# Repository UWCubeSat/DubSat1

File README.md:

# DubSat1 Repository

This is the University of Washington CubeSat Team's DubSat1
library.

More info about our club can be visited [here](http://earthweb.ess.washington.edu/space-propulsion/cubesat.php)

## Repository Contents
DubSat1 is a repository containing configuration-managed assets for the University of Washington's Dubsat-1 (DS-1) satellite, scheduled to fly at the end of the summer 2018.  Assets included here include source code for all subsystems, PCB and schematic design files, and physical design and analysis assets.  

## Repository Branches
The following branches are maintained in the DubSat1 project.  Please follow the guidelines provided.
* master:  Should ALWAYS be kept fully-functional, and ideally tagged to reflect completed milestones/sprint payloads, etc.  *NO CHECKINS SHOULD BE MADE DIRECTLY INTO THIS BRANCH* except by integration managers.
* develop:  Most work should be either committed to this branch, or a feature/* branch based off of develop (see below).  Non-coding work (e.g. PCB board design or SolidWORKS iterations) can go into this branch directly.
* feature/<featurename>:  Most significant chunks of coding work should be done in small, separate feature branches.  Feel free to create these as needed, but do name them using the indicated scheme e.g. "feature/I2Cv2".  However, *BE SURE TO BASE NEW FEATURE BRANCHES OFF OF DEVELOP* and not the master branch.  This helps quite a bit in certain merge scenarios down the road.

## Repository Directories
### /src
Contains the source code designed to run on prototype, test, or flight hardware.  Sub-directories include:

* /src/dsbase:	Here are the core satellite base libraries, used to wrap access to common functionality across the spacecraft, including SPI, I2C and CAN bus access, debug functionality, and general board support packages.
* /src/ssmods:	Standing for "sub-system modules", it is a hard requirement that each subdirectory under ssmods corresponds to one executable unit, to be deployed on one compute element (generally either the MSP430 or MSP432) on the spacecraft, and only the machine-independent files should be saved here (though the .gitignore file SHOULD be setup to screen out most commonly occurring machine-specific build artifacts that we don't want to store).  Anything that doesn't fit this description should go elsewhere.
* /src/devmods:	Used to store experimental work for prototypes or test hardware that is "close" to being moved over to a "real" subsystem module, sort of as a staging ground.  Projects under this folder should also be MSP43x-based, as well.
* /src/dsbase-dev:  GOING AWAY VERY SOON, JeffC will coordinate with folks that typically write to this folder to make the transition to the new branch-based model sometime later in sprint 3.

### /ref
Reference material that is dynamic, including current pin assignments, microcontroller peripheral instance usage, libray usage notes, and Code Composer Studio setup requirements.  Static content - e.g. product datasheets - should be stashed on the team wiki instead.

### /teams
This set of folders is for individual teams to store whatever other assets they have that a) need any level of change tracking, or b) general coordination between multiple contributors, and c) aren't massive.  As a point of reference, each Git repo needs to stay under about 1GB, so if you are routinely checking in 25MB file chunks, please contact the CDH team for alternative arrangements - it can really add up.

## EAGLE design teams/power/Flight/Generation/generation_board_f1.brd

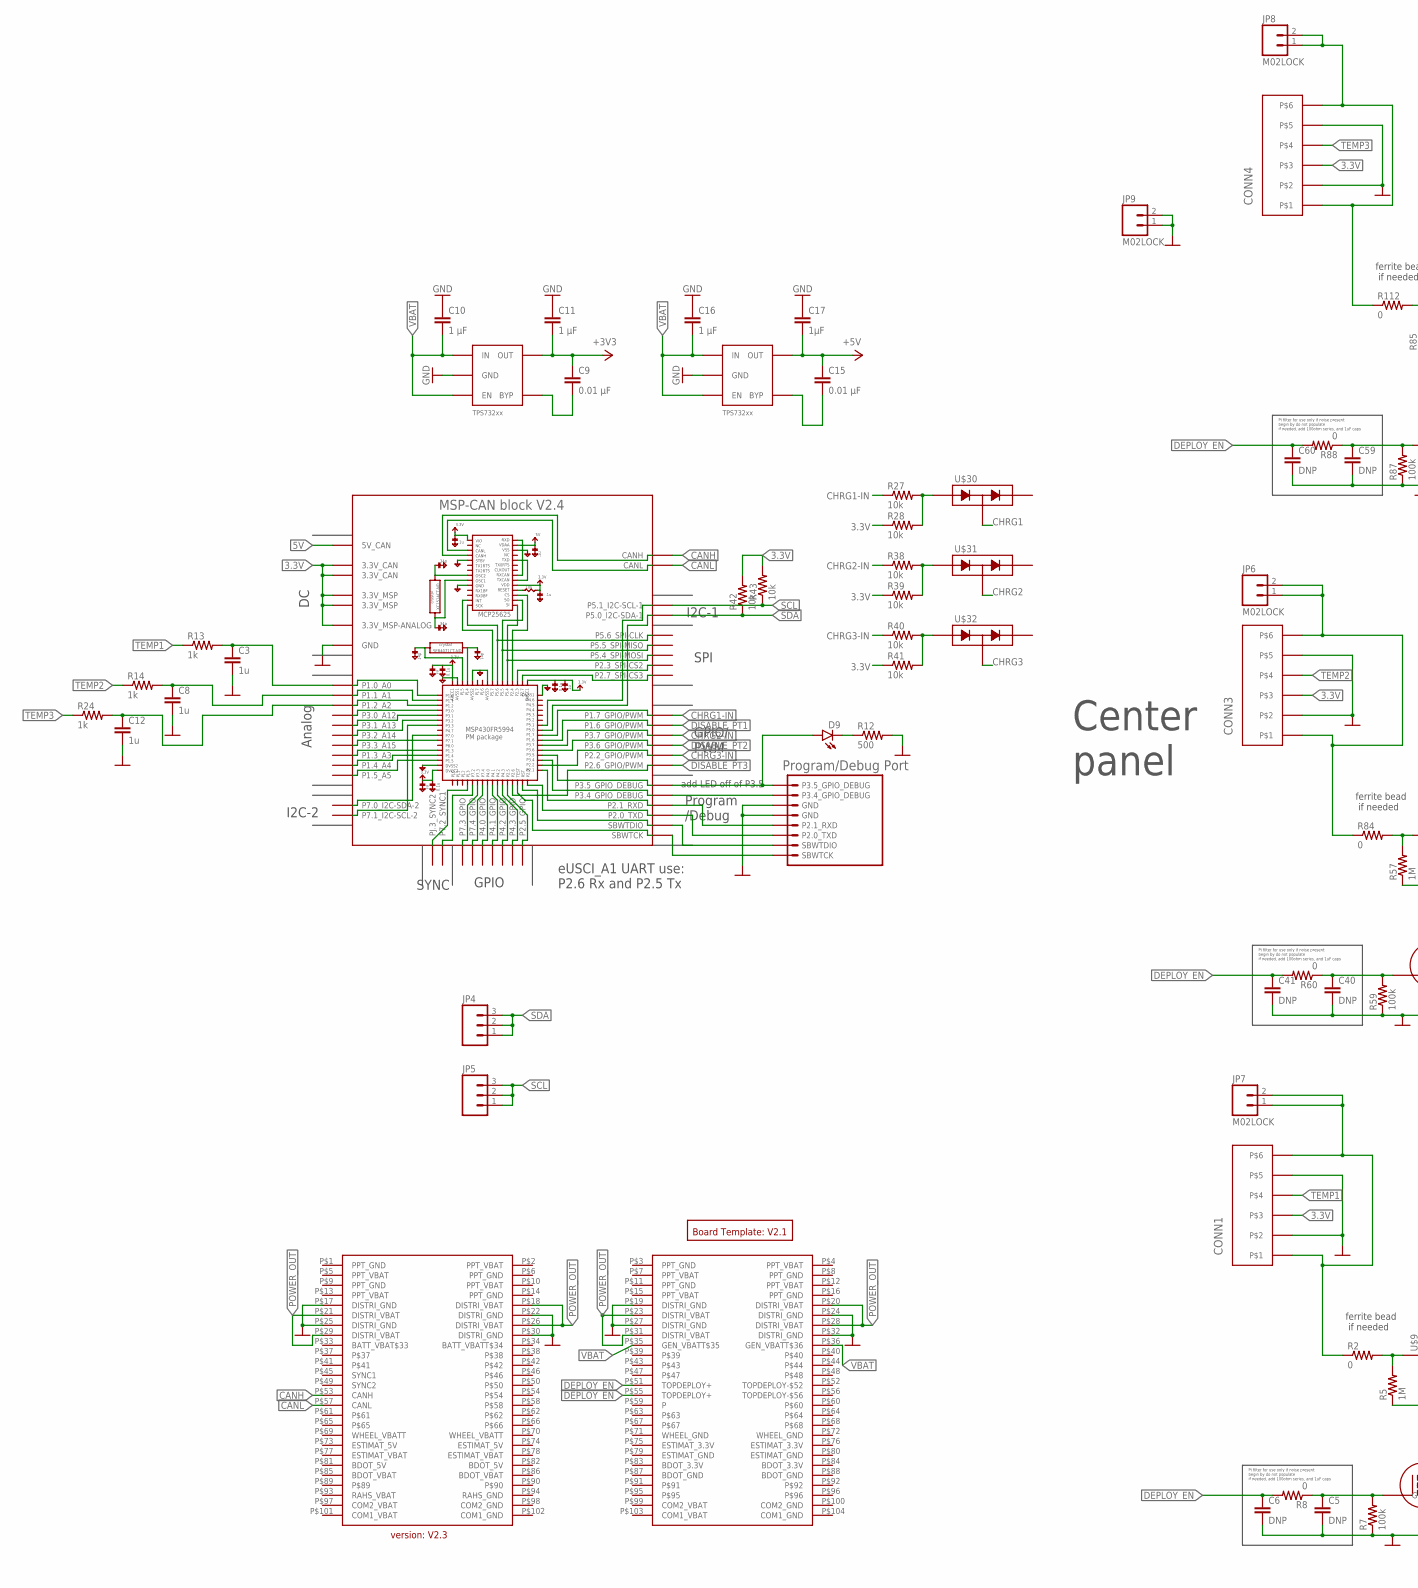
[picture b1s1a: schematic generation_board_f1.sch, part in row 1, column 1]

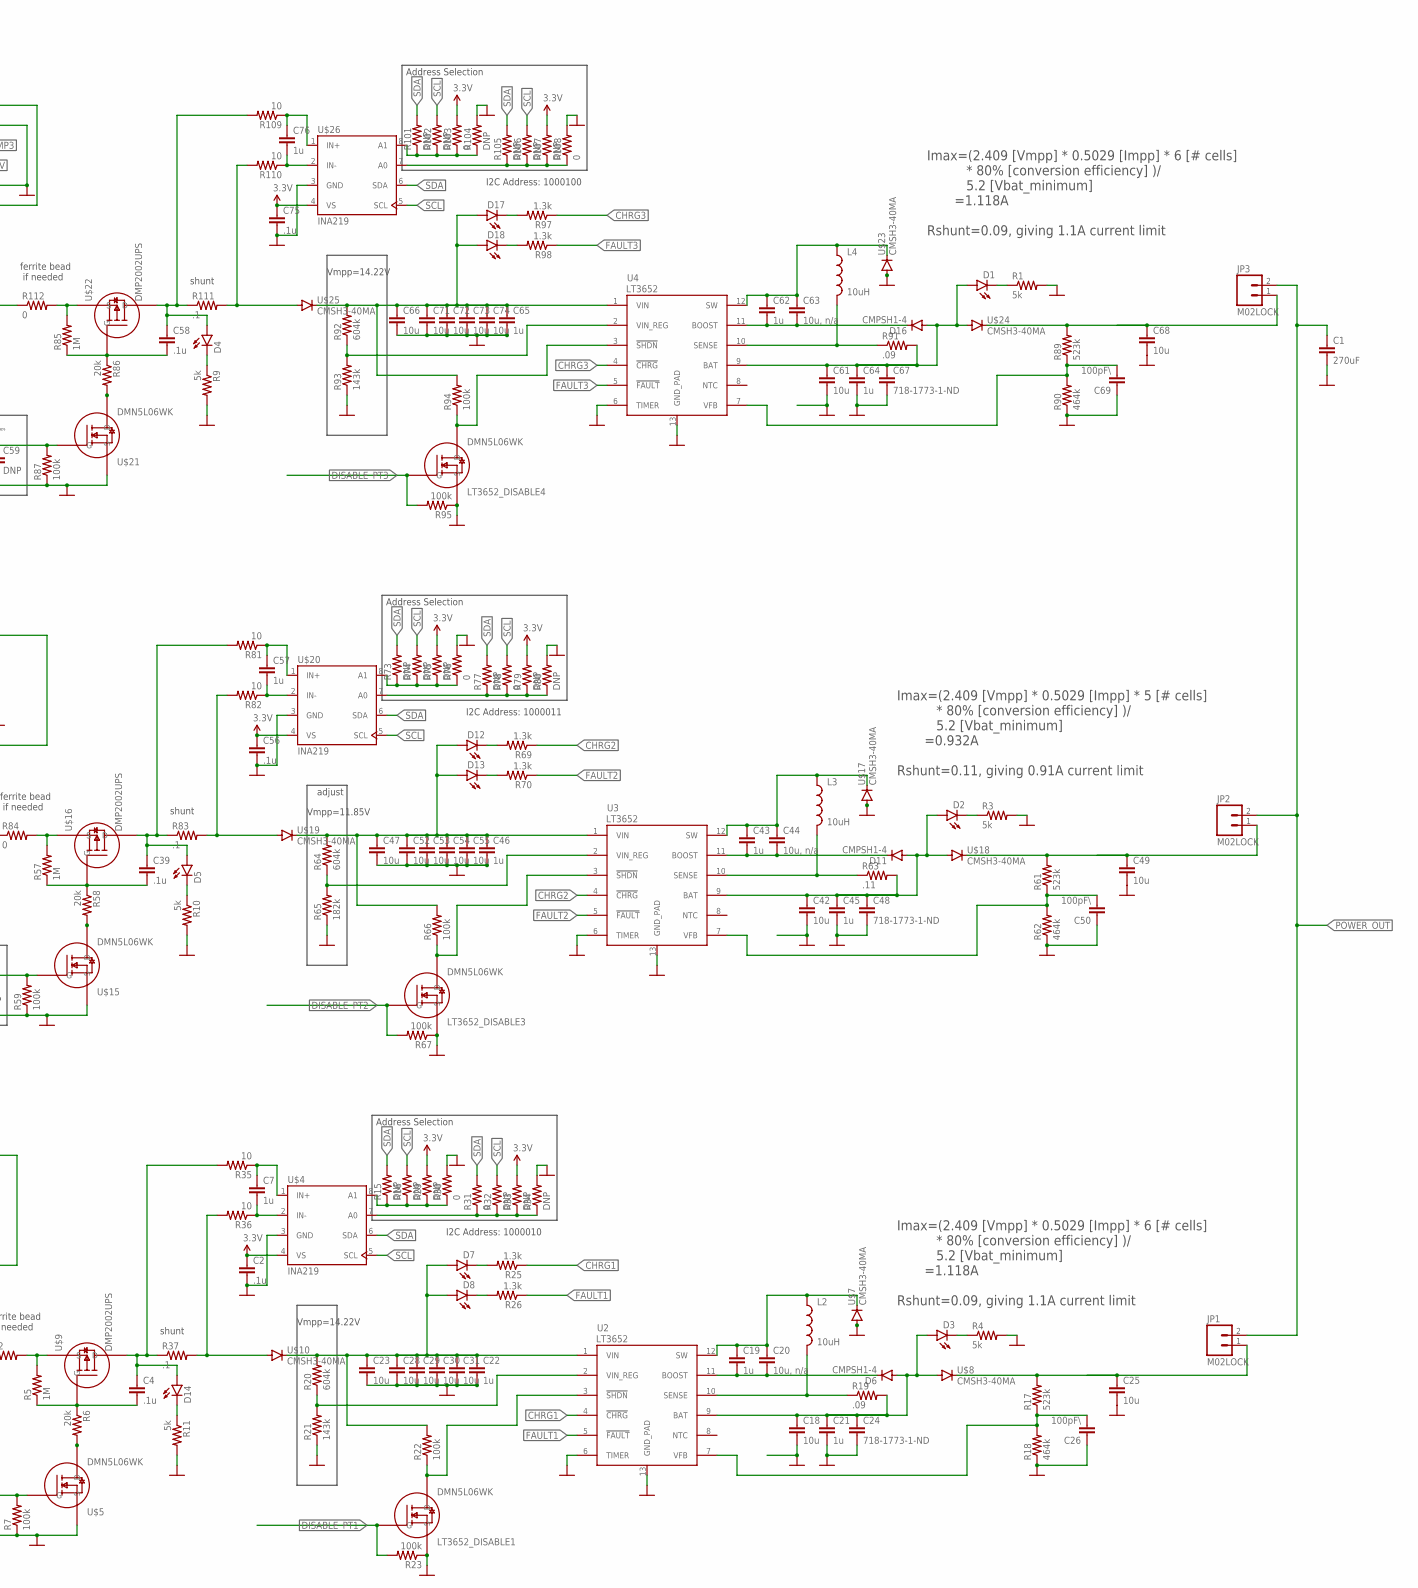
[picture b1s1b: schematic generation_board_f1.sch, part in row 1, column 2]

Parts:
BLK1: MSP-CAN_BLOCK
C1: 270uF; 2917
C2, C4, C39, C56, C58, C75: .1u; 0805
C3, C7, C8, C12, C19, C21, C22, C43, C45, C46, C57, C62, C64, C65, C76: 1u; 0805
C5, C6, C40, C41, C59, C60: DNP; 0805
C9, C15: 0.01 μF; 0805
C10, C11, C16: 1 μF; 0805
C17: 1μF; 0805
C18, C25, C42, C49, C61, C68: 10u; 0805
C20, C44, C63: 10u, n/a; 0805
C23, C28, C29, C30, C31, C47, C52, C53, C54, C55, C66, C71, C72, C73, C74: 10u; 1210
C24, C48, C67: 718-1773-1-ND; 2917
C26, C50, C69: 100pF\; 0805
CONN1, CONN3, CONN4: PICOLOCK_6
D1, D2, D3, D4, D5, D7, D8, D9, D12, D13, D14, D17, D18: LED; LED-1206
D6, D11, D16: CMPSH1-4; SOT23-3
JP1, JP2, JP3, JP6, JP7, JP8, JP9: M02LOCK; 1X02_LOCK
JP4, JP5: M03LOCK; 1X03_LOCK
L2, L3, L4: 10uH; VISHAY_SERIES_01
LT3652_DISABLE1, LT3652_DISABLE3, LT3652_DISABLE4: DMN5L06WK; SOT-323
R1, R3, R4, R9, R10, R11: 5k; 0805
R2, R8, R30, R31, R60, R76, R78, R84, R88, R103, R108, R112: 0; 0805
R5, R57, R85: 1M; 0805
R6, R58, R86: 20k; 0805
R7, R22, R23, R59, R66, R67, R87, R94, R95: 100k; 0805
R12: 500; 0805
R13, R14, R24: 1k; 0805
R15, R16, R29, R32, R33, R34, R73, R74, R75, R77, R79, R80, R101, R102, R104, R105, R106, R107: DNP; 0805
R17, R61, R89: 523k; 0805
R18, R62, R90: 464k; 0805
R19, R91: .09; R2010
R20, R64, R92: 604k; 0805
R21, R93: 143k; 0805
R25, R26, R69, R70, R97, R98: 1.3k; 0805
R27, R28, R38, R39, R40, R41, R42, R43: 10k; 0805
R35, R36, R81, R82, R109, R110: 10; 0805
R37, R83, R111: .1; R2010
R63: .11; R2010
R65: 182k; 0805
U2, U3, U4: LT3652; MSOP-12_GND
U5, U7: TPS732XX; SOT-23-5
U$1: PC104_CONNECTOR
U$2: BOARD_TEMPLATE1; BOARD_TEMPLATE
U$3: PROGRAM/DEBUG_PORT; 1X08_CONNECTOR
U$4, U$20, U$26: INA219; SOT-23-8
U$5, U$15, U$21: DMN5L06WK; SOT-323
U$7, U$8, U$10, U$17, U$18, U$19, U$23, U$24, U$25: CMSH3-40MA; SMA-DIODE
U$9, U$16, U$22: DMP2002UPS; POWERDI5060-8
U$30, U$31, U$32: ONSEMI_DIODE_BAT54SL; SOT23-3

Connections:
3.3V: BLK1.3.3V@CAN1 (3.3V_CAN), BLK1.3.3V@CAN2 (3.3V_CAN), BLK1.3.3V@MSP1 (3.3V_MSP), BLK1.3.3V@MSP2 (3.3V_MSP), BLK1.3.3V_ANALOG@MSP2 (3.3V_MSP-ANALOG), C2.1, C9.1, C11.2, C56.1, C75.1, CONN1.P$3, CONN3.P$3, CONN4.P$3, R28.1, R29.2, R33.2, R39.1, R41.1, R42.2, R43.2, R75.2, R79.2, R103.2, R107.2, U5.P$5 (OUT), U$4.4 (VS), U$20.4 (VS), U$26.4 (VS)
5V: BLK1.5V (5V_CAN), C15.1, C17.2, U7.P$5 (OUT)
BAT1: C18.1, C21.1, C24.1, D3.A, D6.1 (A), R19.2, U2.9 (BAT), U$8.A
BAT2: C42.1, C45.1, C48.1, D2.A, D11.1 (A), R63.2, U3.9 (BAT), U$18.A
BAT3: C61.1, C64.1, C67.1, D1.A, D16.1 (A), R91.2, U4.9 (BAT), U$24.A
BOOST1: C19.2, C20.2, D6.3 (C), U2.11 (BOOST)
BOOST2: C43.2, C44.2, D11.3 (C), U3.11 (BOOST)
BOOST3: C62.2, C63.2, D16.3 (C), U4.11 (BOOST)
CANH: BLK1.CANH, U$1.P$53 (CANH)
CANL: BLK1.CANL, U$1.P$57 (CANL)
CHRG1: R25.1, U2.4 (!CHRG), U$30.3
CHRG1-IN: BLK1.P1.7_GPIO/PWM, R27.1
CHRG2: R69.1, U3.4 (!CHRG), U$31.3
CHRG2-IN: BLK1.P3.7_GPIO/PWM, R38.1
CHRG3: R97.1, U4.4 (!CHRG), U$32.3
CHRG3-IN: BLK1.P2.2_GPIO/PWM, R40.1
DEPLOY_EN: C6.1, C41.1, C60.1, R8.2, R60.2, R88.2, U$1.P$51 (TOPDEPLOY+), U$1.P$55 (TOPDEPLOY+)
DISABLE_PT1: BLK1.P1.6_GPIO/PWM, LT3652_DISABLE1.1 (G), R23.2
DISABLE_PT2: BLK1.P3.6_GPIO/PWM, LT3652_DISABLE3.1 (G), R67.2
DISABLE_PT3: BLK1.P2.6_GPIO/PWM, LT3652_DISABLE4.1 (G), R95.2
FAULT1: R26.1, U2.5 (!FAULT)
FAULT2: R70.1, U3.5 (!FAULT)
FAULT3: R98.1, U4.5 (!FAULT)
GND: BLK1.GND@1 (GND), BLK1.GND@2 (GND), BLK1.GND@3 (GND), BLK1.GND@4 (GND), BLK1.GND@5 (GND), BLK1.GND@7 (GND), BLK1.GND@8 (GND), BLK1.GND@9 (GND), BLK1.GND@10 (GND), BLK1.GND@11 (GND), BLK1.GND@12 (GND), BLK1.GND@13 (GND), BLK1.GND@14 (GND), BLK1.GND@15 (GND), BLK1.GND@16 (GND), BLK1.GND@17 (GND), BLK1.GND@26 (GND), C1.2, C2.2, C3.2, C5.2, C6.2, C8.2, C10.1, C11.1, C12.2, C16.1, C17.1, C18.2, C21.2, C22.2, C23.2, C24.2, C25.2, C26.1, C28.2, C29.2, C30.2, C31.2, C40.2, C41.2, C42.2, C45.2, C46.2, C47.2, C48.2, C49.2, C50.1, C52.2, C53.2, C54.2, C55.2, C56.2, C59.2, C60.2, C61.2, C64.2, C65.2, C66.2, C67.2, C68.2, C69.1, C71.2, C72.2, C73.2, C74.2, C75.2, CONN1.P$2, CONN1.P$5, CONN3.P$2, CONN3.P$5, CONN4.P$2, CONN4.P$5, JP9.1, JP9.2, LT3652_DISABLE1.2 (S), LT3652_DISABLE3.2 (S), LT3652_DISABLE4.2 (S), R1.2, R3.2, R4.2, R7.1, R9.2, R10.2, R11.2, R12.2, R18.1, R21.1, R23.1, R30.2, R34.2, R59.1, R62.1, R65.1, R67.1, R76.2, R80.2, R87.1, R90.1, R93.1, R95.1, R104.2, R108.2, U2.6 (TIMER), U2.13 (GND_PAD), U3.6 (TIMER), U3.13 (GND_PAD), U4.6 (TIMER), U4.13 (GND_PAD), U5.P$2 (GND), U7.P$2 (GND), U$1.P$17 (DISTRI_GND), U$1.P$19 (DISTRI_GND), U$1.P$22 (DISTRI_GND), U$1.P$24 (DISTRI_GND), U$1.P$25 (DISTRI_GND), U$1.P$27 (DISTRI_GND), U$1.P$30 (DISTRI_GND), U$1.P$32 (DISTRI_GND), U$3.5 (GND), U$3.6 (GND), U$4.3 (GND), U$5.2 (S), U$7.A, U$15.2 (S), U$17.A, U$20.3 (GND), U$21.2 (S), U$23.A, U$26.3 (GND)
IN1: R2.2, R5.2, U$9.S1 (S), U$9.S2 (S), U$9.S3 (S)
IN2: R57.2, R84.2, U$16.S1 (S), U$16.S2 (S), U$16.S3 (S)
IN3: R85.2, R112.2, U$22.S1 (S), U$22.S2 (S), U$22.S3 (S)
INA219_A0_1: R31.1, R32.1, R33.1, R34.1, U$4.7 (A0)
INA219_A0_2: R77.1, R78.1, R79.1, R80.1, U$20.7 (A0)
INA219_A0_3: R105.1, R106.1, R107.1, R108.1, U$26.7 (A0)
INA219_A1_1: R15.1, R16.1, R29.1, R30.1, U$4.8 (A1)
INA219_A1_2: R73.1, R74.1, R75.1, R76.1, U$20.8 (A1)
INA219_A1_3: R101.1, R102.1, R103.1, R104.1, U$26.8 (A1)
INA219_IN+_1: C7.1, R35.1, U$4.1 (IN+)
INA219_IN+_2: C57.1, R81.1, U$20.1 (IN+)
INA219_IN+_3: C76.1, R109.1, U$26.1 (IN+)
INA219_IN-_1: C7.2, R36.1, U$4.2 (IN-)
INA219_IN-_2: C57.2, R82.1, U$20.2 (IN-)
INA219_IN-_3: C76.2, R110.1, U$26.2 (IN-)
INPUT_PANEL1: CONN1.P$1, CONN1.P$6, JP7.1, JP7.2, R2.1
INPUT_PANEL2: CONN3.P$1, CONN3.P$6, JP6.1, JP6.2, R84.1
INPUT_PANEL3: CONN4.P$1, CONN4.P$6, JP8.1, JP8.2, R112.1
LDO_3V3_BYP2: C9.2, U5.P$4 (BYP)
LDO_5V_BYP2: C15.2, U7.P$4 (BYP)
LOAD1: R36.2, R37.2, U$10.A
LOAD2: R82.2, R83.2, U$19.A
LOAD3: R110.2, R111.2, U$25.A
unnamed: C4.2, R5.1, R6.1, U$9.G
unnamed: C5.1, R7.2, R8.1, U$5.1 (G)
unnamed: BLK1.P3.5_GPIO_DEBUG, D9.A, U$3.8 (P3.5_GPIO_DEBUG)
unnamed: BLK1.P3.4_GPIO_DEBUG, U$3.7 (P3.4_GPIO_DEBUG)
unnamed: BLK1.P2.1_RXD, U$3.4 (P2.1_RXD)
unnamed: R6.2, U$5.3 (D)
unnamed: BLK1.P2.0_TXD, U$3.3 (P2.0_TXD)
unnamed: BLK1.SBWTDIO, U$3.2 (SBWTDIO)
unnamed: BLK1.SBWTCK, U$3.SBWTCK
unnamed: D1.C, R1.1
unnamed: D2.C, R3.1
unnamed: D3.C, R4.1
unnamed: D4.C, R9.1
unnamed: C39.2, R57.1, R58.1, U$16.G
unnamed: C40.1, R59.2, R60.1, U$15.1 (G)
unnamed: LT3652_DISABLE1.3 (D), R22.1, U2.3 (!SHDN)
unnamed: D8.C, R26.2
unnamed: D7.C, R25.2
unnamed: R58.2, U$15.3 (D)
unnamed: BLK1.P1.1_A1, C8.1, R14.2
unnamed: D9.C, R12.1
unnamed: LT3652_DISABLE3.3 (D), R66.1, U3.3 (!SHDN)
unnamed: D13.C, R70.2
unnamed: D12.C, R69.2
unnamed: D14.C, R11.1
unnamed: D5.C, R10.1
unnamed: C58.2, R85.1, R86.1, U$22.G
unnamed: C59.1, R87.2, R88.1, U$21.1 (G)
unnamed: R86.2, U$21.3 (D)
unnamed: LT3652_DISABLE4.3 (D), R94.1, U4.3 (!SHDN)
unnamed: D18.C, R98.2
unnamed: D17.C, R97.2
unnamed: BLK1.P1.2_A2, C12.1, R24.2
unnamed: BLK1.P1.0_A0, C3.1, R13.2
unnamed: R27.2, R28.2, U$30.1
unnamed: R38.2, R39.2, U$31.1
unnamed: R40.2, R41.2, U$32.1
OUT1: C4.1, D14.A, R35.2, R37.1, U$9.D1 (D), U$9.D2 (D), U$9.D3 (D), U$9.D4 (D), U$9.D5 (D)
OUT2: C39.1, D5.A, R81.2, R83.1, U$16.D1 (D), U$16.D2 (D), U$16.D3 (D), U$16.D4 (D), U$16.D5 (D)
OUT3: C58.1, D4.A, R109.2, R111.1, U$22.D1 (D), U$22.D2 (D), U$22.D3 (D), U$22.D4 (D), U$22.D5 (D)
OUTPUT1: C25.1, JP1.1, R17.2, U$8.C
OUTPUT2: C49.1, JP2.1, R61.2, U$18.C
OUTPUT3: C68.1, JP3.1, R89.2, U$24.C
POWER_OUT: C1.1, JP1.2, JP2.2, JP3.2, U$1.P$18 (DISTRI_VBAT), U$1.P$20 (DISTRI_VBAT), U$1.P$21 (DISTRI_VBAT), U$1.P$23 (DISTRI_VBAT), U$1.P$26 (DISTRI_VBAT), U$1.P$28 (DISTRI_VBAT), U$1.P$29 (DISTRI_VBAT), U$1.P$31 (DISTRI_VBAT)
SCL: BLK1.P5.1_I2C-SCL-1, JP5.1, JP5.2, JP5.3, R16.2, R32.2, R43.1, R74.2, R78.2, R102.2, R106.2, U$4.5 (SCL), U$20.5 (SCL), U$26.5 (SCL)
SDA: BLK1.P5.0_I2C-SDA-1, JP4.1, JP4.2, JP4.3, R15.2, R31.2, R42.1, R73.2, R77.2, R101.2, R105.2, U$4.6 (SDA), U$20.6 (SDA), U$26.6 (SDA)
SENSE1: L2.P$2 (2), R19.1, U2.10 (SENSE)
SENSE2: L3.P$2 (2), R63.1, U3.10 (SENSE)
SENSE3: L4.P$2 (2), R91.1, U4.10 (SENSE)
SW1: C19.1, C20.1, L2.P$1 (1), U2.12 (SW), U$7.C
SW2: C43.1, C44.1, L3.P$1 (1), U3.12 (SW), U$17.C
SW3: C62.1, C63.1, L4.P$1 (1), U4.12 (SW), U$23.C
TEMP1: CONN1.P$4, R13.1
TEMP2: CONN3.P$4, R14.1
TEMP3: CONN4.P$4, R24.1
VBAT: C10.2, C16.2, U5.P$1 (IN), U5.P$3 (EN), U7.P$1 (IN), U7.P$3 (EN), U$1.P$35 (GEN_VBATT$35), U$1.P$36 (GEN_VBATT$36)
VFB1: C26.2, R17.1, R18.2, U2.7 (VFB)
VFB2: C50.2, R61.1, R62.2, U3.7 (VFB)
VFB3: C69.2, R89.1, R90.2, U4.7 (VFB)
VIN1: C22.1, C23.1, C28.1, C29.1, C30.1, C31.1, D7.A, D8.A, R20.2, R22.2, U2.1 (VIN), U$10.C
VIN2: C46.1, C47.1, C52.1, C53.1, C54.1, C55.1, D12.A, D13.A, R64.2, R66.2, U3.1 (VIN), U$19.C
VIN3: C65.1, C66.1, C71.1, C72.1, C73.1, C74.1, D17.A, D18.A, R92.2, R94.2, U4.1 (VIN), U$25.C
VIN_REG1: R20.1, R21.2, U2.2 (VIN_REG)
VIN_REG2: R64.1, R65.2, U3.2 (VIN_REG)
VIN_REG3: R92.1, R93.2, U4.2 (VIN_REG)

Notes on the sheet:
Pi filter for use only if noise present begin by do not populate if needed, add 100ohm series, and 1uF caps
Address Selection
ferrite bead if needed
shunt
adjust
Vmpp=14.22V
Center panel
Imax=(2.409 [Vmpp] * 0.5029 [Impp] * 6 [# cells] * 80% [conversion efficiency] )/ 5.2 [Vbat_minimum] =1.118A Rshunt=0.09, giving 1.1A current limit
Imax=(2.409 [Vmpp] * 0.5029 [Impp] * 5 [# cells] * 80% [conversion efficiency] )/ 5.2 [Vbat_minimum] =0.932A Rshunt=0.11, giving 0.91A current limit
Vmpp=11.85V
I2C Address: 1000010
I2C Address: 1000011
I2C Address: 1000100

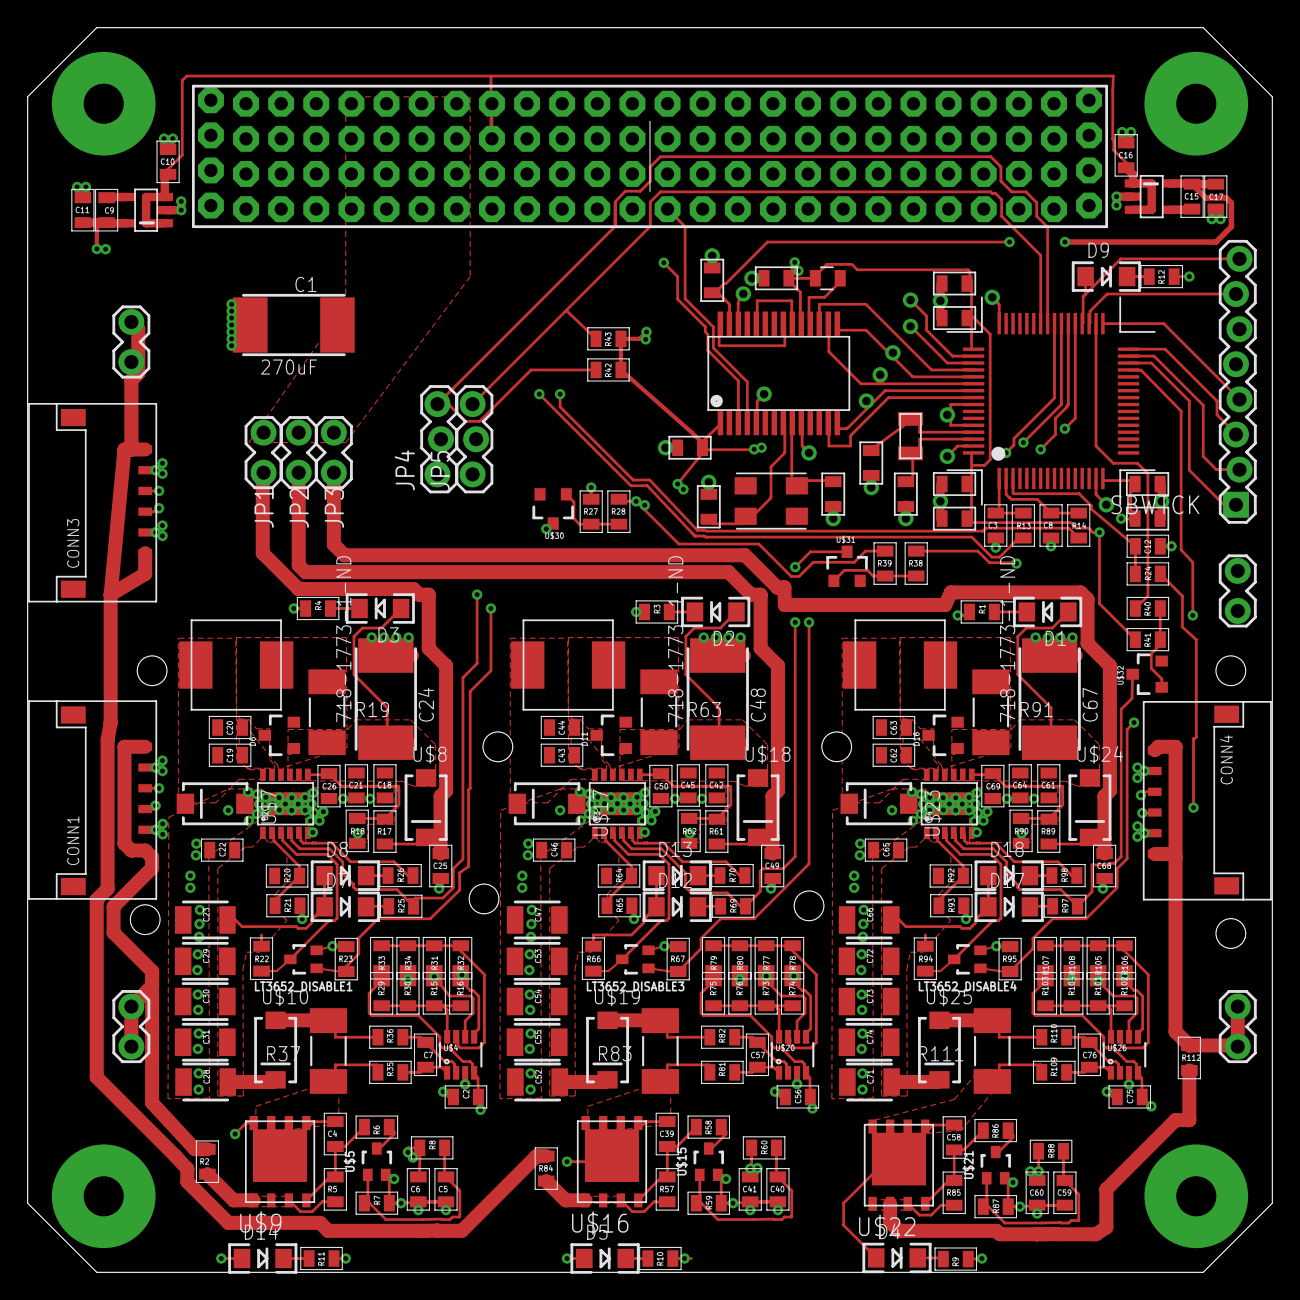
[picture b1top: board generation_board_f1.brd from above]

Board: 4 copper layers, 90.0 x 90.0 mm, 229 parts (0 on the bottom side), 112 nets.

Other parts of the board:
U$6, U$11, U$12, U$13, U$14, U$27, U$28, U$29: #2-56_BOLT_HOLE

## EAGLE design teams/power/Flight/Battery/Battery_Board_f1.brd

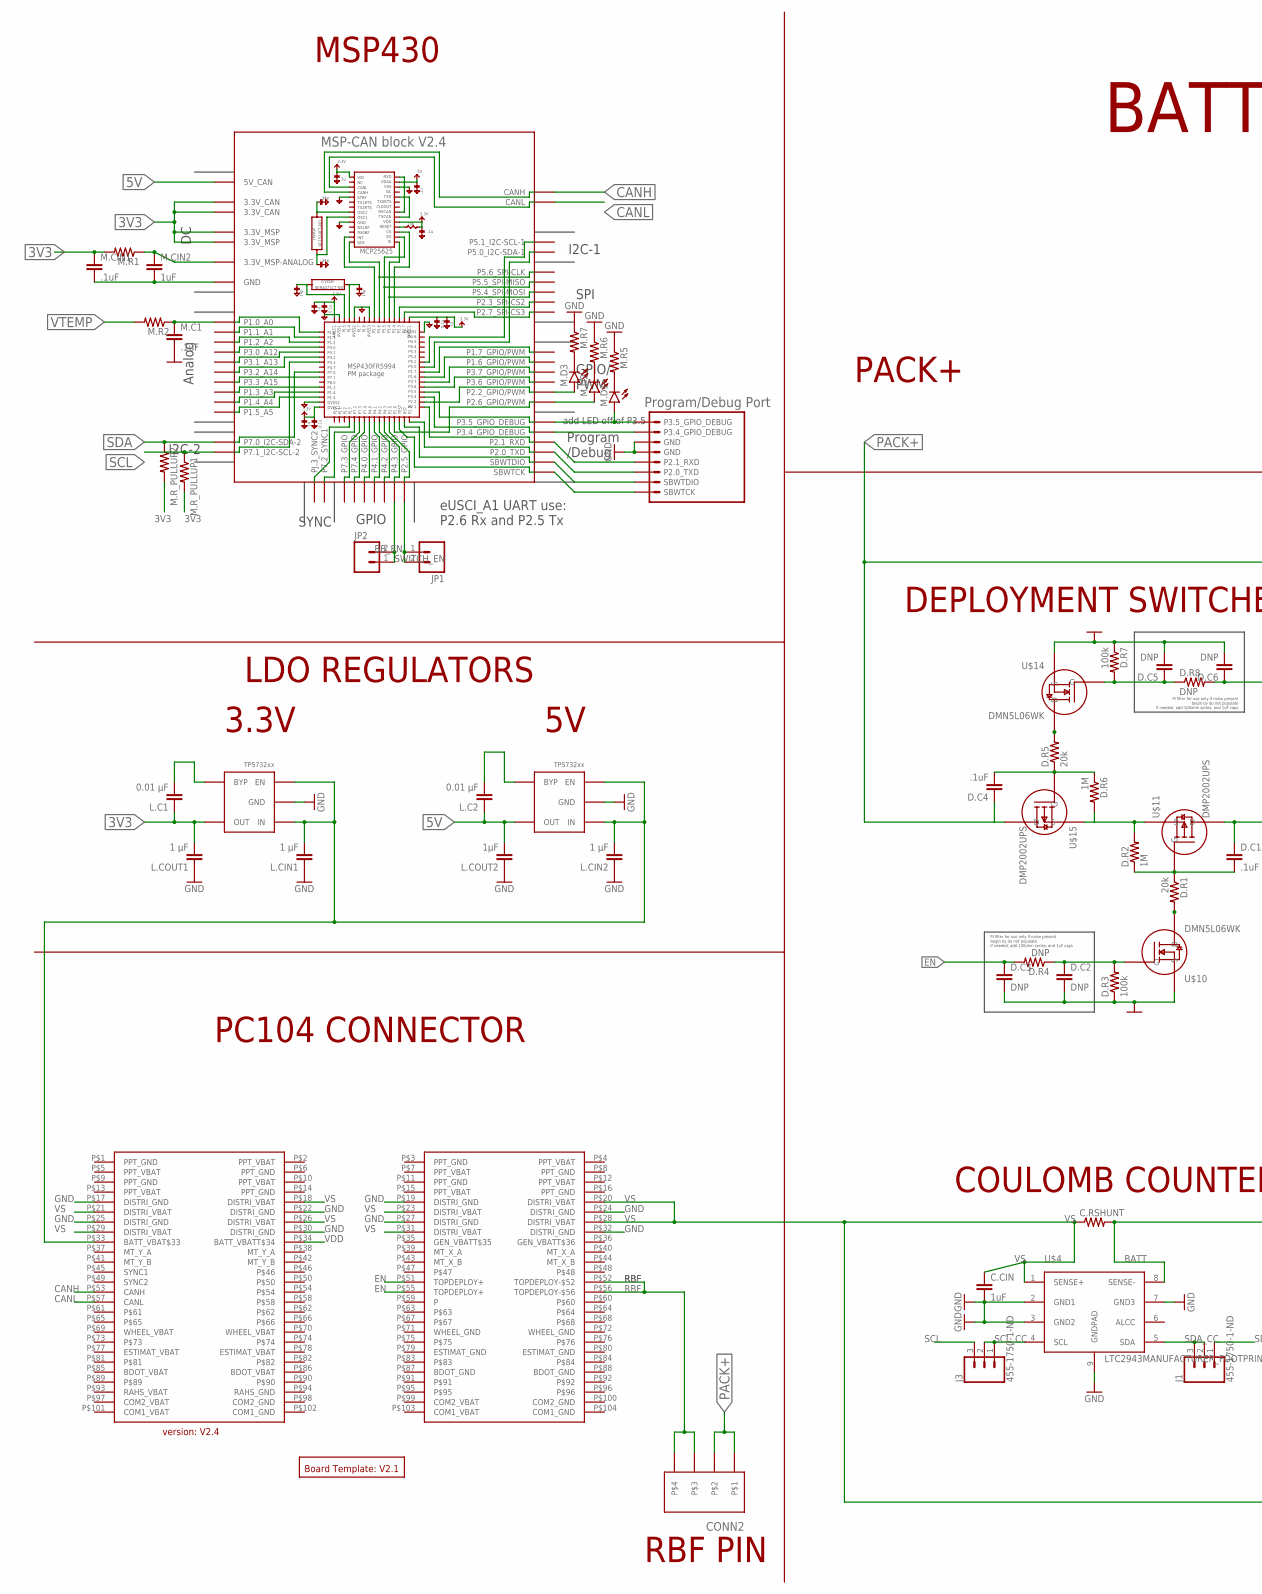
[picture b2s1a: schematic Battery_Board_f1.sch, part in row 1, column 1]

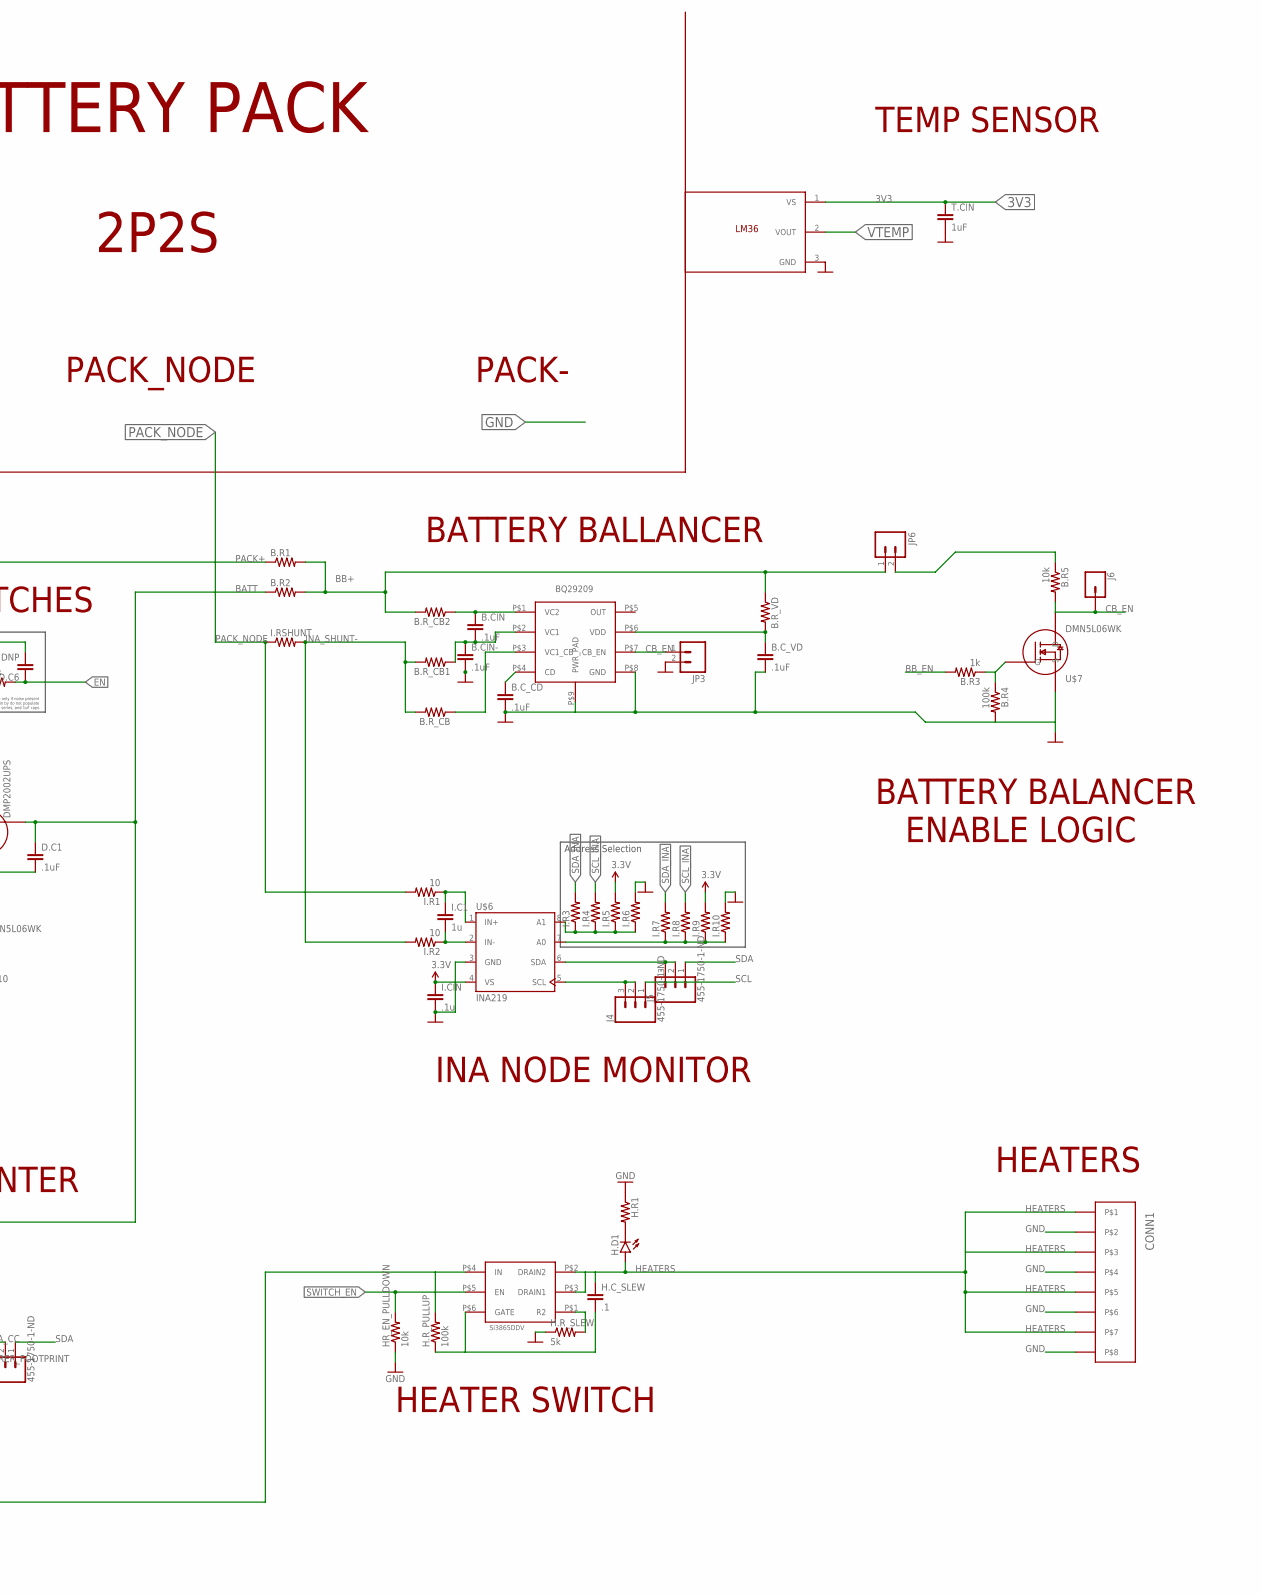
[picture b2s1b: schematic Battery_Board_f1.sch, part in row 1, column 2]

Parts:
B.CIN, B.CIN-, B.C_CD, B.C_VD: .1uF; 0805
B.R1, B.R2, B.R_CB, B.R_CB1, B.R_CB2, B.R_VD: RESISTOR0805; 0805
B.R3: 1k; 0805
B.R4: 100k; 0805
B.R5: 10k; 0805
BLK1: MSP-CAN_BLOCK
C.CIN: 1uF; 0805
C.RSHUNT: RESISTOR2512; R2512
CONN1: PICOLOCK_8PICOLOCK_8; PICOLOCK_8
CONN2: PICOLOCK_4PICOLOCK_4; PICOLOCK_4
D.C1, D.C4: .1uF; 0805
D.C2, D.C3, D.C5, D.C6, D.R4, D.R8: DNP; 0805
D.R1, D.R5: 20k; 0805
D.R2, D.R6: 1M; 0805
D.R3, D.R7: 100k; 0805
H.C_SLEW: .1; 0805
H.D1: LED; LED-1206
H.R1: RESISTOR0805; 0805
H.R_PULLUP: 100k; 0805
H.R_SLEW: 5k; 0805
HR_EN_PULLDOWN: 10k; 0805
I.C1: 1u; 0805
I.CIN: .1u; 0805
I.R1, I.R2: 10; 0805
I.R3, I.R4, I.R5, I.R6, I.R7, I.R8, I.R9, I.R10: RESISTOR0805; 0805
I.RSHUNT: RESISTOR2010; R2010
J1, J3, J4, J5: 455-1750-1-ND; 1X03
J6: CONN_01; 1X01
JP1, JP2, JP3, JP6: M02LOCK; 1X02_LOCK
L.C1, L.C2: 0.01 μF; 0805
L.CIN1, L.CIN2, L.COUT1: 1 μF; 0805
L.COUT2: 1μF; 0805
M.C1, M.CIN1: .1uF; 0805
M.CIN2: 1uF; 0805
M.D1, M.D2, M.D3: LED; LED-1206
M.R1, M.R2, M.R5, M.R6, M.R7, M.R_PULLUP1, M.R_PULLUP2: RESISTOR0805; 0805
T.CIN: 1uF; 0805
U1, U4: TPS732XX; SOT-23-5
U$1: BOARD_TEMPLATE3D; BOARD_TEMPLATE
U$2: PC104_CONNECTOR
U$4: LTC2943MANUFACTURER_FOOTPRINT; DFN-8_DD
U$5: BQ29209; VSON8
U$6: INA219; SOT-23-8
U$7, U$10, U$14: DMN5L06WK; SOT-323
U$8: LM36; TO-92-3
U$11, U$15: DMP2002UPS; POWERDI5060-8
U$12: PROGRAM/DEBUG_PORT; 1X08_CONNECTOR
U$16: SI3865DDV; TSOP-6

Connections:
3V3: BLK1.3.3V@CAN1 (3.3V_CAN), BLK1.3.3V@CAN2 (3.3V_CAN), BLK1.3.3V@MSP1 (3.3V_MSP), BLK1.3.3V@MSP2 (3.3V_MSP), I.CIN.1, I.R5.2, I.R9.2, L.C1.1, L.COUT1.2, M.CIN1.1, M.R1.2, M.R_PULLUP1.2, M.R_PULLUP2.2, T.CIN.1, U1.P$5 (OUT), U$6.4 (VS), U$8.1 (VS)
3V3_MSP-ANALOG: BLK1.3.3V_ANALOG@MSP2 (3.3V_MSP-ANALOG), M.CIN2.1, M.R1.1
5V: BLK1.5V (5V_CAN), L.C2.1, L.COUT2.2, U4.P$5 (OUT)
BATT: B.R2.1, C.RSHUNT.2, D.C1.1, U$4.8 (SENSE-), U$11.D1 (D), U$11.D2 (D), U$11.D3 (D), U$11.D4 (D), U$11.D5 (D)
BB+: B.R1.2, B.R2.2, B.R_CB2.2, B.R_VD.1, JP6.1
BB_EN: B.R3.2, BLK1.P4.3_GPIO, JP2.1, JP2.2
CANH: BLK1.CANH, U$2.P$53 (CANH)
CANL: BLK1.CANL, U$2.P$57 (CANL)
CB_EN: B.R5.2, J6.1, JP3.1, U$5.P$7 (CB_EN), U$7.3 (D)
EN: D.C3.1, D.C6.1, D.R4.2, D.R8.2, U$2.P$51 (TOPDEPLOY+), U$2.P$55 (TOPDEPLOY+)
GND: B.CIN-.2, B.C_CD.2, B.C_VD.2, B.R4.2, BLK1.GND@1 (GND), BLK1.GND@2 (GND), BLK1.GND@3 (GND), BLK1.GND@4 (GND), BLK1.GND@5 (GND), BLK1.GND@7 (GND), BLK1.GND@8 (GND), BLK1.GND@9 (GND), BLK1.GND@10 (GND), BLK1.GND@11 (GND), BLK1.GND@12 (GND), BLK1.GND@13 (GND), BLK1.GND@14 (GND), BLK1.GND@15 (GND), BLK1.GND@16 (GND), BLK1.GND@17 (GND), BLK1.GND@26 (GND), C.CIN.2, CONN1.P$2, CONN1.P$4, CONN1.P$6, CONN1.P$8, D.C2.2, D.C3.2, D.C5.2, D.C6.2, D.R3.1, D.R7.1, H.R1.1, H.R_SLEW.1, HR_EN_PULLDOWN.1, I.CIN.2, I.R6.2, I.R10.2, JP3.2, L.CIN1.1, L.CIN2.1, L.COUT1.1, L.COUT2.1, M.C1.2, M.CIN1.2, M.CIN2.2, M.R5.1, M.R6.1, M.R7.1, T.CIN.2, U1.P$2 (GND), U4.P$2 (GND), U$2.P$17 (DISTRI_GND), U$2.P$19 (DISTRI_GND), U$2.P$22 (DISTRI_GND), U$2.P$24 (DISTRI_GND), U$2.P$25 (DISTRI_GND), U$2.P$27 (DISTRI_GND), U$2.P$30 (DISTRI_GND), U$2.P$32 (DISTRI_GND), U$4.2 (GND1), U$4.3 (GND2), U$4.7 (GND3), U$4.9 (GNDPAD), U$5.P$8 (GND), U$5.P$9 (PWR_PAD), U$6.3 (GND), U$7.2 (S), U$8.3 (GND), U$10.2 (S), U$12.5 (GND), U$12.6 (GND), U$14.2 (S)
HEATERS: CONN1.P$1, CONN1.P$3, CONN1.P$5, CONN1.P$7, H.C_SLEW.1, H.D1.A, U$16.P$2 (DRAIN2), U$16.P$3 (DRAIN1)
IN: D.R2.2, D.R6.2, U$11.S1 (S), U$11.S2 (S), U$11.S3 (S), U$15.S1 (S), U$15.S2 (S), U$15.S3 (S)
INA219_A0_1: I.R7.1, I.R8.1, I.R9.1, I.R10.1, U$6.7 (A0)
INA219_A1_1: I.R3.1, I.R4.1, I.R5.1, I.R6.1, U$6.8 (A1)
INA219_IN+_1: I.C1.1, I.R1.1, U$6.1 (IN+)
INA219_IN-_1: I.C1.2, I.R2.1, U$6.2 (IN-)
INA_SHUNT-: B.R_CB.2, B.R_CB1.2, I.R2.2, I.RSHUNT.2
LDO_3V3_BYP1: L.C1.2, U1.P$4 (BYP)
LDO_5V_BYP1: L.C2.2, U4.P$4 (BYP)
unnamed: BLK1.P3.5_GPIO_DEBUG, M.D1.A, U$12.8 (P3.5_GPIO_DEBUG)
unnamed: B.R5.1, JP6.2
unnamed: BLK1.P3.4_GPIO_DEBUG, U$12.7 (P3.4_GPIO_DEBUG)
unnamed: BLK1.P2.1_RXD, U$12.4 (P2.1_RXD)
unnamed: B.CIN.1, B.R_CB2.1, U$5.P$1 (VC2)
unnamed: B.CIN.2, B.CIN-.1, B.R_CB1.1, U$5.P$2 (VC1)
unnamed: D.C1.2, D.R1.1, D.R2.1, U$11.G
unnamed: D.C2.1, D.R3.2, D.R4.1, U$10.1 (G)
unnamed: B.R_CB.1, U$5.P$3 (VC1_CB)
unnamed: B.C_CD.1, U$5.P$4 (CD)
unnamed: D.R1.2, U$10.3 (D)
unnamed: B.R3.1, B.R4.1, U$7.1 (G)
unnamed: B.C_VD.1, B.R_VD.2, U$5.P$6 (VDD)
unnamed: D.C4.2, D.R5.1, D.R6.1, U$15.G
unnamed: D.C5.1, D.R7.2, D.R8.1, U$14.1 (G)
unnamed: D.R5.2, U$14.3 (D)
unnamed: BLK1.P2.0_TXD, U$12.3 (P2.0_TXD)
unnamed: BLK1.SBWTDIO, U$12.2 (SBWTDIO)
unnamed: BLK1.SBWTCK, U$12.SBWTCK
unnamed: M.D1.C, M.R5.2
unnamed: BLK1.P1.0_A0, M.C1.1, M.R2.1
unnamed: M.D2.C, M.R6.2
unnamed: M.D3.C, M.R7.2
unnamed: H.R_SLEW.2, U$16.P$1 (R2)
unnamed: H.C_SLEW.2, H.R_PULLUP.1, U$16.P$6 (GATE)
unnamed: BLK1.P2.2_GPIO/PWM, M.D3.A
unnamed: BLK1.P2.6_GPIO/PWM, M.D2.A
unnamed: H.D1.C, H.R1.2
PACK+: B.R1.1, CONN2.P$1, CONN2.P$2, D.C4.1, U$15.D1 (D), U$15.D2 (D), U$15.D3 (D), U$15.D4 (D), U$15.D5 (D)
PACK_NODE: I.R1.2, I.RSHUNT.1
RBF: CONN2.P$3, CONN2.P$4, U$2.P$52 (TOPDEPLOY-$52), U$2.P$56 (TOPDEPLOY-$56)
SCL: BLK1.P7.1_I2C-SCL-2, J3.3, J4.1, M.R_PULLUP1.1
SCL_CC: J3.1, J3.2, U$4.4 (SCL)
SCL_INA: I.R4.2, I.R8.2, J4.2, J4.3, U$6.5 (SCL)
SDA: BLK1.P7.0_I2C-SDA-2, J1.1, J5.1, M.R_PULLUP2.1
SDA_CC: J1.2, J1.3, U$4.5 (SDA)
SDA_INA: I.R3.2, I.R7.2, J5.2, J5.3, U$6.6 (SDA)
SWITCH_EN: BLK1.P2.5_GPIO, HR_EN_PULLDOWN.2, JP1.1, JP1.2, U$16.P$5 (EN)
VDD: L.CIN1.2, L.CIN2.2, U1.P$1 (IN), U1.P$3 (EN), U4.P$1 (IN), U4.P$3 (EN), U$2.P$33 (BATT_VBAT$33), U$2.P$34 (BATT_VBATT$34)
VS: C.CIN.1, C.RSHUNT.1, H.R_PULLUP.2, U$2.P$18 (DISTRI_VBAT), U$2.P$20 (DISTRI_VBAT), U$2.P$21 (DISTRI_VBAT), U$2.P$23 (DISTRI_VBAT), U$2.P$26 (DISTRI_VBAT), U$2.P$28 (DISTRI_VBAT), U$2.P$29 (DISTRI_VBAT), U$2.P$31 (DISTRI_VBAT), U$4.1 (SENSE+), U$16.P$4 (IN)
VTEMP: M.R2.2, U$8.2 (VOUT)

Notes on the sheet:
Address Selection
Pi filter for use only if noise present begin by do not populate if needed, add 100ohm series, and 1uF caps
BATTERY PACK
2P2S
PACK+
PACK_NODE
PACK-
DEPLOYMENT SWITCHES
COULOMB COUNTER
HEATER SWITCH
HEATERS
LDO REGULATORS
3.3V
INA NODE MONITOR
BATTERY BALLANCER
BATTERY BALANCER ENABLE LOGIC
TEMP SENSOR
MSP430
PC104 CONNECTOR
RBF PIN

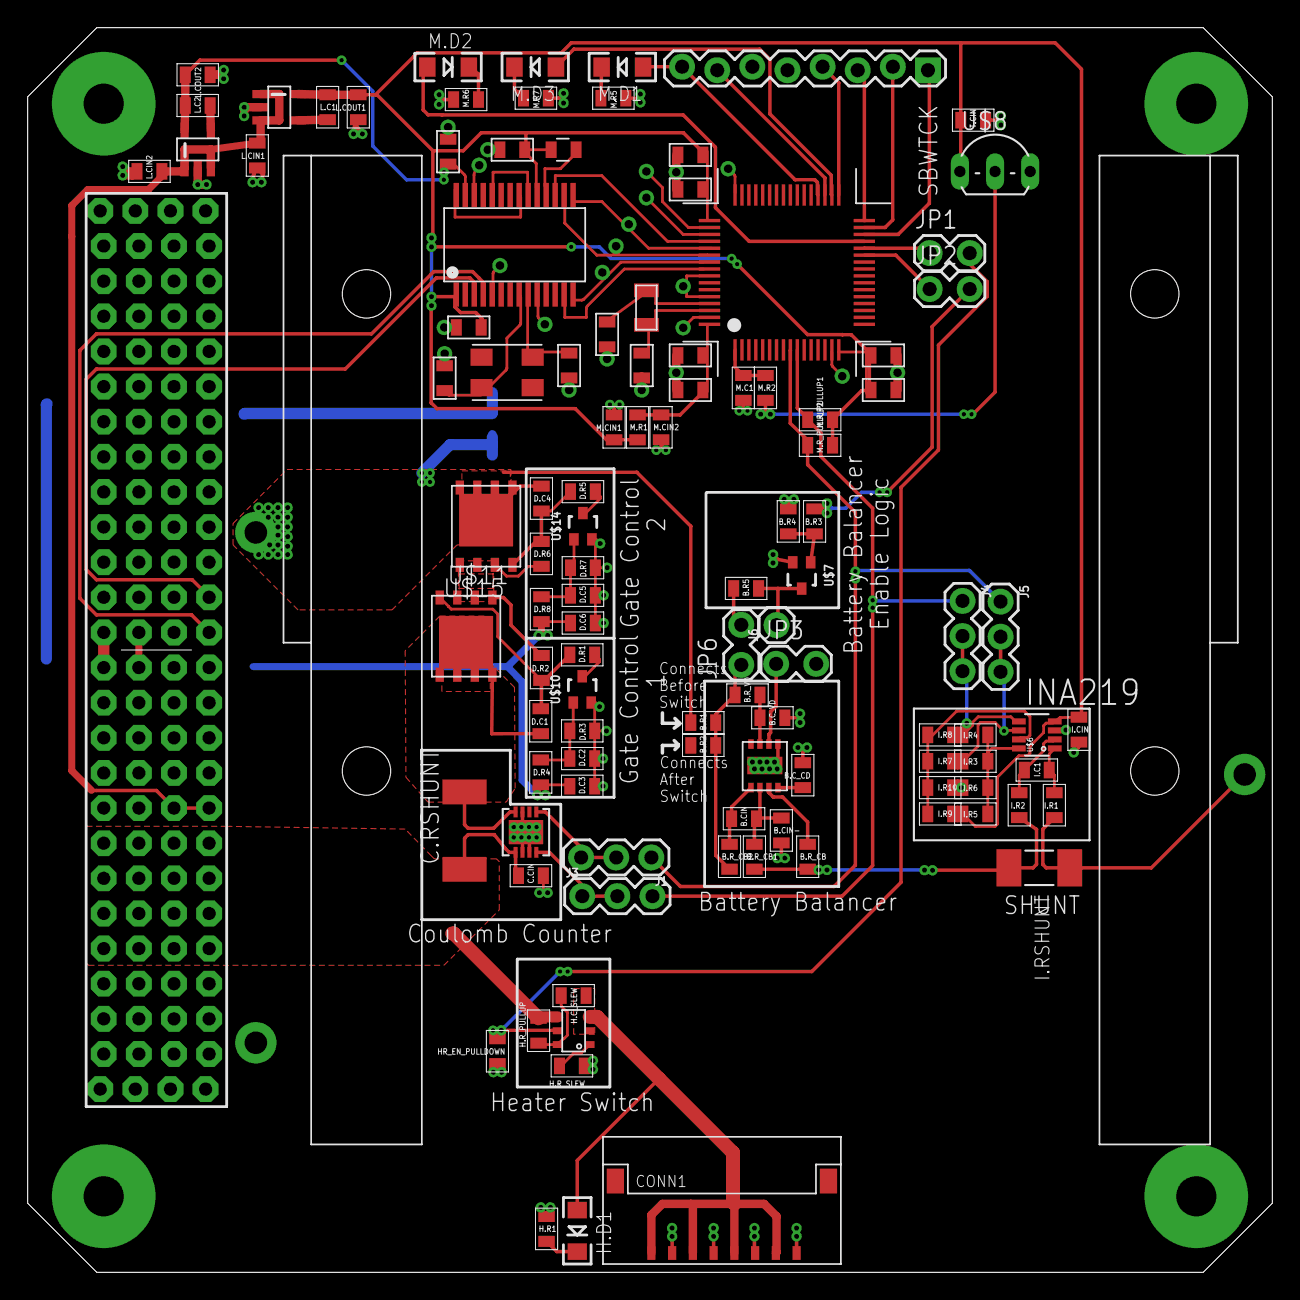
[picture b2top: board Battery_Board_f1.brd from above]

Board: 2 copper layers, 90.0 x 90.0 mm, 96 parts (1 on the bottom side), 61 nets.

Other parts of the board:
U$9: BATTERY_HOLDERS

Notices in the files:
parts and their libraries:
SparkFun-Connectors: Licensing: Creative Commons ShareAlike 4.0 International - https://creativecommons.org/licenses/by-sa/4.0
dicons: Copyright (C) 2004, Bob Starr (rtzaudio@mindspring.com)
